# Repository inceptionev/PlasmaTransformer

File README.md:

# Plasma Transformer

## An open-source plasma toroid project by inceptionev (Dr. Bunga)

This project mainly focuses on creating a driver and 3D-printed support structure that allows for safe continuous operation of a plasma toroid.  The objectives are stable operation of a levitating halo of plasma at maximum height above the coil and protection against touching energized components, while providing airflow to keep both the electronics and the globe cool.  The globes are filled with a low-pressure of xenon gas.

### Key Features of this project:
- Plasma Driver PCB with experimentation-friendly features:
  - Wide input power range from 12-60V for easy power control.  Onboard 12V supply for stable fan and gate drive.
  - High-voltage auto-igniter strikes the plasma whenever plasma is not present, but also does not load the driver when plasma is live.  This helps prevent damage from runaway unloaded oscillation.  Designed in collaboration with @ltwin0.
  - Oscillation detector illuminates to show when the driver is in oscillation, whether or not plasma is present.  Based on a design from Sky-guided.
  - Socketed coil and tank capacitor connectors for easy tuning.
  - Dedicated on-board oscilloscope probes on the MOSFET gate and drain nets for Class-E tuning.  Connect an SMA cable directly from the board to a terminator and the oscilloscope.
  - Selectable Gate-Source cap via jumper headers to tune AC gate drive strenth.
  - Separate power switch and DC Gate Bias control.  Turn it off and on without changing the DC gate bias level.
- 3D printed cooling shroud:
  - Provides directed airflow for cooling both the electronics and the globe for continuous use.
  - Supports the fan, board, coil, and globe with ideal spacing for achieving a levitating plasma halo.
  - Provides attachments for rubber bands to hold the globe in place for environments where the device may be in motion, or to attach a shade to make the plasma more visible in outdoor installations.
  - Includes a cover and coil ring that keeps curious fingers away from the hazardous high-voltage parts. (But caution is always advised around high voltage and RF)
- 3D-printed assembly aids:
  - Coil forms for ease of making the plasma coil.

Special thanks to:  
Sky-guided, whose inductive oscillation indicator design is used in this project.  
@ltwin8, whose RF node parasitic auto-igniter design is used in this project and was detailed in https://github.com/inceptionev/PlasmaTransformer/issues/1  

Native design files and manufacturing files in gerber and stl format are provided for the 20cm and 13cm globe sizes.

KiCAD PCB files are found in the /Plasma Transformer PCB folder.  If you want to edit the design, the files are in the folder.  If you just want to make the boards, you need:
- Plasma Transformer PCB/manufacturing/[the zip file with the latest rev]
- Plasma Transformer PCB/bom/[the bom file matching that rev]

Rev 5 PCB specific note:
The holes for the capacitor sockets are too large, so instead of being press-fit, they will need to be soldered in.  I recommend using a piece of paper tape to hold them in place on the top side, then soldering them on the bottom side.  Or you can skip the sockets and solder in the capacitors directly.

3d print design files and a dxf for the heatsink hole pattern are found in the 3D Print and CNC folder.  The heatsink holes are all M3 drill/tap.

If you are doing turnkey PCBA assembly, you probably want to DNP the fan (M1), heatsink (HS1), MOSFET (Q1), and tank capacitors (C1, C16-20) from the BOM in the Turnkey Assembly ZIP package, as you will assemble these later.

If you just want to print the files, look here:
- /3D Print and CNC/20cm Globe STL 3D Print Set
- /3D Print and CNC/13cm Globe STL 3D Print Set

## Additional Materials Needed:
- 12 AWG magnet wire (2mm dia)
- 12mm or 1/2" polyimide (kapton) tape
- 4x M4*30mm self tapping screws
- 4x M4*8mm self tapping screws
- 4x M3 6x6mm Male/Female threaded standoff
- 4x M3 6mm screws to mount PCB to heatsink
- M3 washers and lockwashers
- JST XHP-2 connector and contacts for fan
- The appropriate capacitor values from the list below
- Thermal pad for TO-247 MOSFET (example: SPK4-0.006-00-104)
- M3*20mm screw, washer, and lockwasher for mounting MOSFET
- 4mm OD x 2.5mm ID PTFE tube (commonly sold as Bowden tube for 1.75mm filament 3D printers)

## Assembly instructions:
- I recommend 3D-printing the coil forms and the spacer ring first, then the cooling shroud, cover, and foot.  You may also want to print a smaller coil form for pre-winding in the first batch, see coil instructions below.
- The main cooling shroud may take 20+ hrs to print, so you can build the heatsink, coil and PCB while it is printing.
- Prepare the heatsink
  - Drill and tap the holes in the heatsink.  They are all M3.  A DXF is provided if you wnat to use a CNC.
  - Mount the MOSFET into the heatsink with thermal pad LOOSELY (do not tighten yet)
  - Bend the MOSFET pins up 90 degrees
  - Install the standoffs into the heatsink
- Assemble the PCB per the BOM EXCEPT for the MOSFET.  That component will be soldered last.
- Mount the PCB to the heatsink with 4x M3x6mm screws, washers, and lockwashers, threading the MOSFET pins through the holes in the board.  Make sure the MOSFET is loose so it can move into alighment with the board.
- Tighten the screws mounting the PCB to the heatsink first.
- Then tighten the mounting screw of the MOSFET to the heatsink.
- Solder the MOSFET in.
- Add connector to the fan.  Pin 1 is positive.
- Make the coil
  - Print out the coil form in the folder for the globe size you are using.
  - Push a length of 12AWG magnet wire in a length of insulating PTFE tube.  It helps if the tube and the wire are both straight.  Taping them to the edge of a table will accomplish this.
    - For the 13cm globe, push 171.6cm of wire into 151.6cm of PTFE tube.  Leave 10cm of wire sticking out at both ends.
	- For the 20cm globe, push 203cm of wire into 175cm of of PTFE tube.  Leave 14cm of wire sticking out at both ends.
  - First wrap the wire and insulator around an object slightly smaller than the coil form.  This will make wrapping on the coil form easier.  You can use the 13cm coil form as the pre-wind form for the 20cm coil. An stl file for an 80mm coil form is also provided to act as the pre-wind for the 13cm coil.
  - Wrap the slightly-smaller coil of wire and insulator onto the coil form.  Start at the lip, and work up from there in a clockwise direction with the lip facing away from you.  This ensures that the bottom coil connects to the RF Node (the right block on the PCB).  This is the higher voltage terminal, and having it on the bottom coil helps with levitation of the plasma.
    - 13cm Globe: you should get 4 coils, minus the 9mm gap where the ends meet.
	- 20cm Globe: you should get 3 coils, minus the 9mm gap where the ends meet.
  - Use the slots in the coil form to tape up the coil so it holds its shape.  Polyimide (Kapton) tape is recommended.
  - Remove the coil from the form and wrap the coil again where the tail meets the coil
  - Open the coil terminal latches on the PCB and fit the coil into the assembly with the PCB, making bends to allow for the envelope of the globe.  Make an 'S' curve at the bottom of the coil wires where they exit the PCB blocks, to allow for adjusting the height.
  - Trim the coil tails if necessary.
  - Burn about 12mm of insulation off the end of the coil tails and clean it up with sandpaper until you can see the shiny copper underneath.  A lighter works well for this.
  - Install the coil spacer ring into the top of the coil, opposite of the direction where the wire tails go.
- Mount the foot and the fan to the bottom with the M4*30mm screws, threading the fan wires through the notch in the bottom.  
- Connect the fan to the PCB.  On the 20mm cooling shroud, a slot is provided in the wall next to the PCB to hold the fan connector temporarily for easy connecting and disconnecting.
- Mount the PCB to the cooling shroud with the M4*8mm screws
- Latch the coil into the PCB.
- Screw in 5x M4x8mm screws into the bosses around the circumference of the cooling shroud. This can be used for shrouds or rubber bands to secure the globe.
- Optionally install the cover into the cooling shroud.

## Known successful values from experimentation:

Supply Voltage:
- 20cm Globe: 24V
- 13cm Globe: 19V

Gate-Drain Cap:
- 20cm Globe: none
- 13cm Globe: none

Resonant Cap:
- 20cm Globe: 3x 24pF 564RC0GAJ602EJ240J
- 13cm Globe: 3x 24pF 564RC0GAJ602EJ240J

Gate-Source Cap:
- 20cm Globe: 2.7nF + 3.6nF + 1.8nF + 1.8nF
- 13cm Globe: 2.7nF

Measured Air Core Inductance of Globe Coils (no globe or plasma present):
- 13cm Globe, 4 turns 122mm x 16mm long: 3.3uH
- 20cm Globe, 3 turns 187mm dia x 12mm long: 3.6uH

## Tips and Tricks for Experimenting with Plasma Toroids:
- The goal of feedback tuning is to minimize the source-drain voltage across the MOSFET during the points of switching, otherwise it will get hot quickly.
- Also be mindful of the voltage rating on the cap between the plasma globe coil and the gate.  This cap will see 1000V+ when the coil is unloaded (when there is no plasma).
- Also be careful of anything in that node.  That means anything between the gate-coil capacitor and the coil, including the bottom turns of the coil.  This is the HF node, aka RF node, where the highest amplitude of voltage oscillation is seen.  It will burn you if you touch it, sometimes even touching insulated portions.  The burn is nearly painless at first, and then painful later.
- The MOSFET and the coil-gate cap are the two most common components to break in this circuit.
- Haloplasma is a good source for the xenon-filled plasma globes.

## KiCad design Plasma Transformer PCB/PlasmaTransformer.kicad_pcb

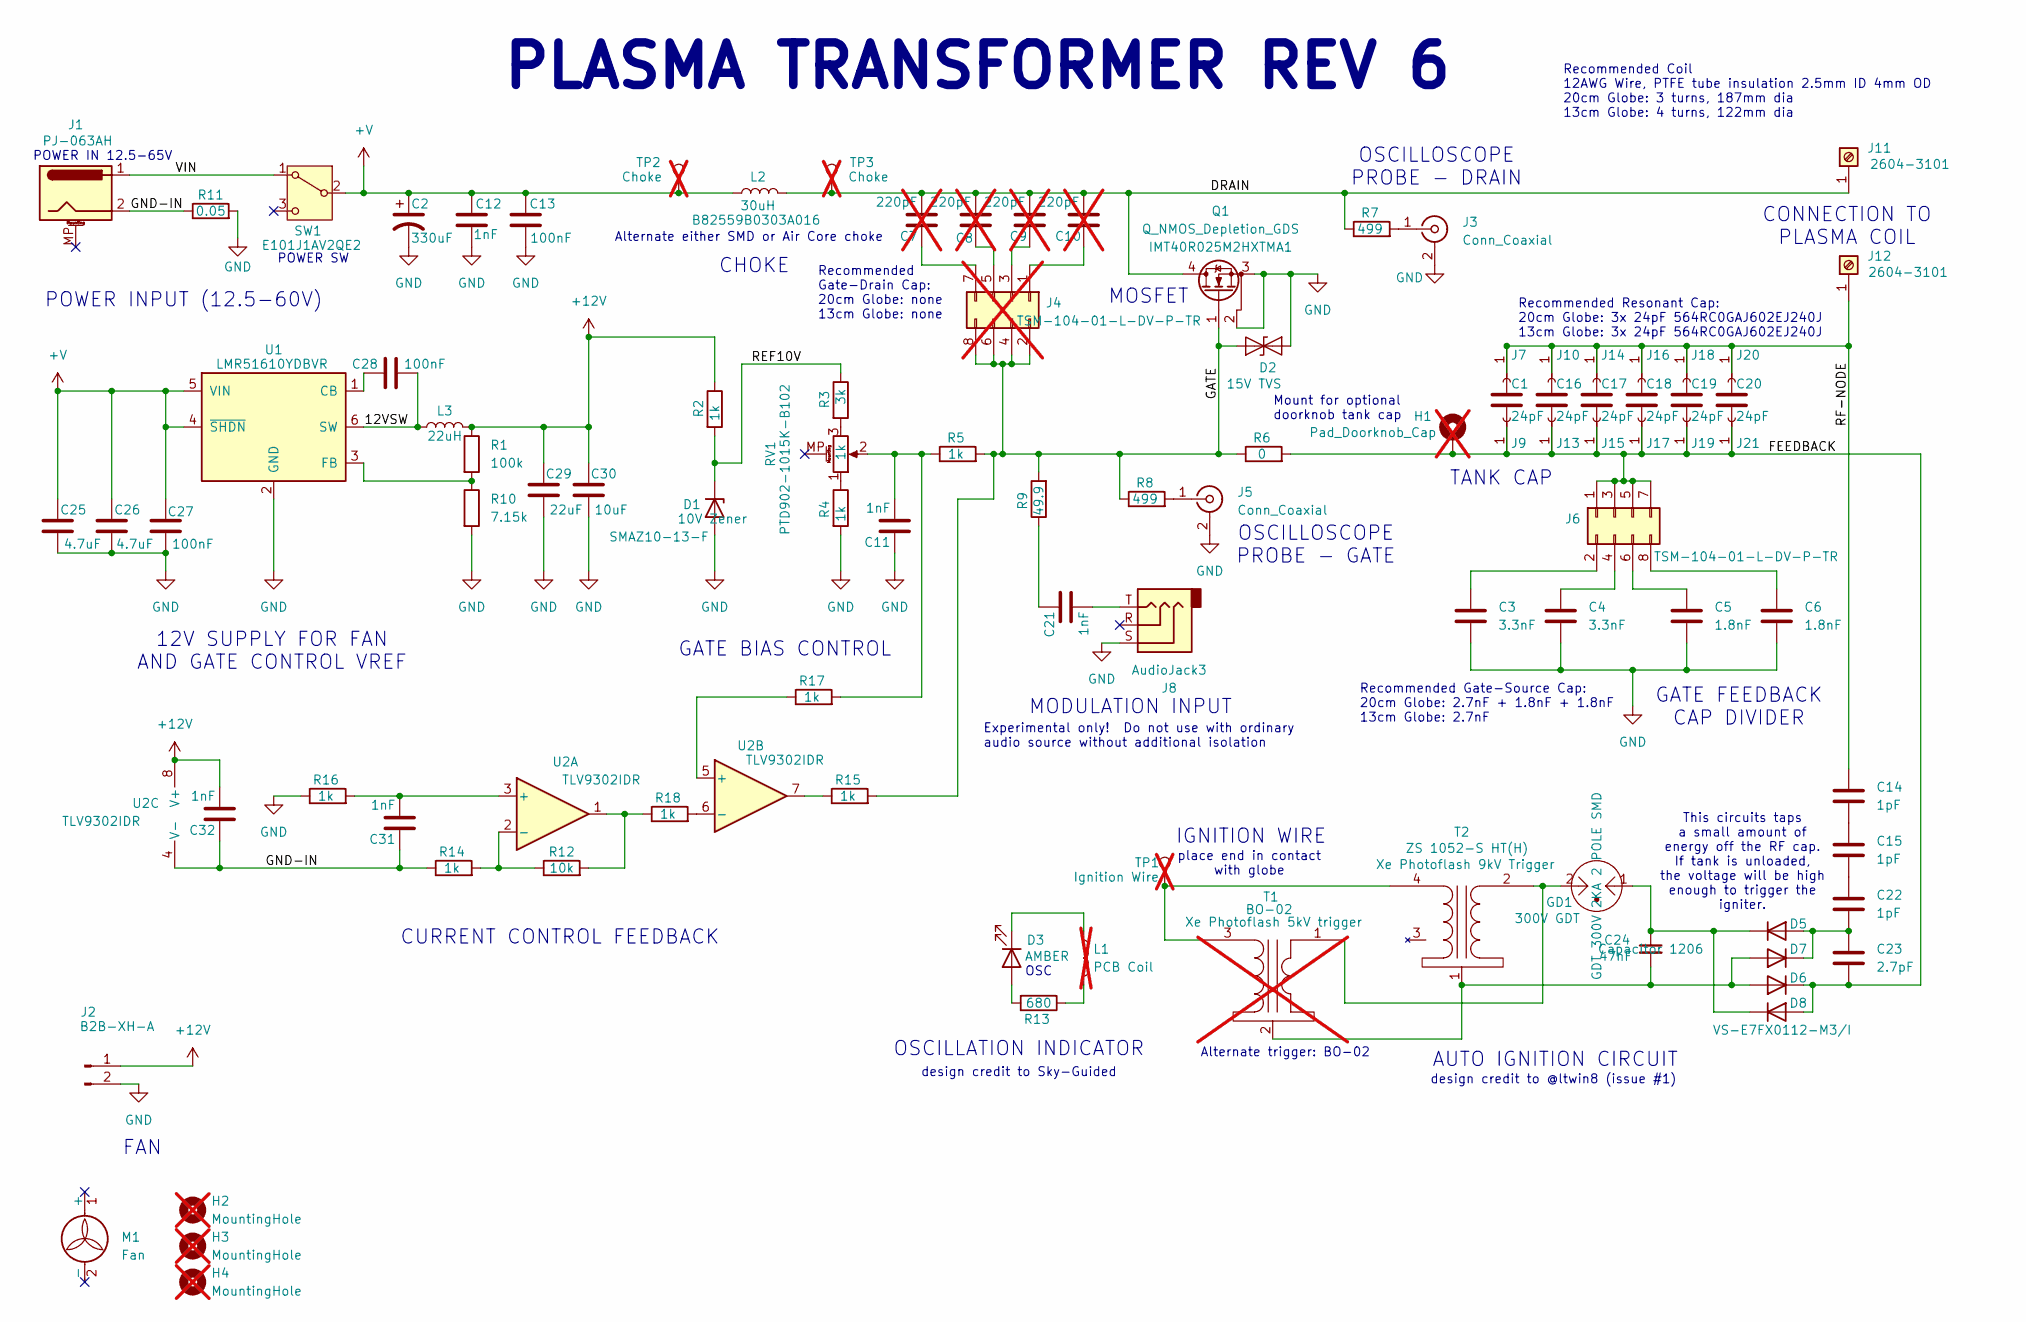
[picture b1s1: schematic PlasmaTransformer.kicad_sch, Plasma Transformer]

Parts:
C1, C16, C17, C18, C19, C20: 24pF; C_Disc_D11.0mm_W5.0mm_P10.00mm; Voltage 6000V; MPN 564RC0GAJ602EJ240J
C2: 330uF; CP_Elec_16x17.5_FK_Series; Voltage 80V; MPN EEV-FK1K331M
C3, C4: 3.3nF; C_1206_3216Metric; Voltage 250V; MPN C3216C0G2E332K085AA
C5, C6: 1.8nF; C_1206_3216Metric; Voltage 630V; MPN CC1206JKNPOZBN182
C7, C8, C9, C10: 220pF; C_1206_3216Metric; Voltage 1000V; MPN VJ1206A221JBGTW1HV; not fitted
C11, C12, C21, C31, C32: 1nF; C_0805_2012Metric; Voltage 100V; MPN CL21C102JCFNNNE
C13: 100nF; C_1812_4532Metric; Voltage 1000V; MPN GRM43DR7LW104KW01K
C14, C15, C22: 1pF; C_1210_3225Metric; Voltage 2000V; MPN 111122K01P00BQTAF9LM
C23: 2.7pF; C_1210_3225Metric; Voltage 2000V; MPN 111122K02P70HQTAF9LM
C24: 47nF; C_1206_3216Metric; Voltage 500V; MPN C1206C473KCRACTU
C25, C26: 4.7uF; C_1210_3225Metric; Voltage 100V; MPN CL32B475KCVZW6E
C27, C28: 100nF; C_0805_2012Metric; Voltage 100V; MPN C2012X7R2A104K125AA
C29: 22uF; C_0805_2012Metric; Voltage 25V; MPN CL21A226MAYNNNE
C30: 10uF; C_0805_2012Metric; Voltage 25V; MPN CL21A106KAYNNNE
D1: 10V Zener; D_SMA; MPN SMAZ10-13-F
D2: 15V TVS; D_SMC; MPN 5.0SMDJ15CA
D3: AMBER; LED_1206_3216Metric; MPN 150120AS75000
D5, D6, D7, D8: D; D_SMF; Voltage 1200V; MPN VS-E7FX0112-M3/I
GD1: 300V GDT; L_1812_4532Metric; MPN 2051-30-SM-RPLF
H1: Pad_Doorknob_Cap; MountingHole_5.3mm_M5_Pad; not fitted
H2, H3, H4: MountingHole; MountingHole_3.2mm_M3; not fitted
J1: Barrel_Jack_MountingPin; BarrelJack_CUI_PJ-063AH_Horizontal; MPN PJ-063AH
J2: Conn_01x02_Pin; JST_XH_B2B-XH-A_1x02_P2.50mm_Vertical; MPN B2B-XH-A
J3, J5: Conn_Coaxial; SMA_Amphenol_901-144_Vertical; MPN RFPC-SMA28-F
J4: Conn_02x04_Odd_Even; PinHeader_2x04_P2.54mm_Vertical_SMD; MPN TSM-104-01-L-DV-P-TR; not fitted
J6: Conn_02x04_Odd_Even; PinHeader_2x04_P2.54mm_Vertical_SMD; MPN TSM-104-01-L-DV-P-TR
J7, J9, J10, J13, J14, J15, J16, J17, J18, J19, J20, J21: Conn_01x01_Socket; H8501-05; MPN H8501-05
J8: AudioJack3; Jack_3.5mm_CUI_SJ-3523-SMT_Horizontal; MPN SJ-3523-SMT-TR
J11, J12: Screw_Terminal_01x01; CONN_2604-3101_WAG; MPN 2604-3101
L1: PCB Coil; FEEDBACK_COIL_B; not fitted
L2: 30uH; B82559B_TDK; MPN B82559B0303A016
L3: 22uH; L_Pana_PCC-KVP_5.5x5mm; MPN ETQ-P3M220KVP
M1: Fan; FAN AXIAL 92X25.4MM; MPN AFB0912VHD-F00
Q1: Q_NMOS_Depletion_GDS; IMT40R025M2HXTMA1; MPN IMT40R025M2HXTMA1
R1: 100k; R_0805_2012Metric; Tolerance 1%; MPN RC0805FR-07100KL
R2, R4, R5, R14, R15, R16, R17, R18: 1k; R_0805_2012Metric; Tolerance 1%; MPN RC0805FR-071KL
R3: 3k; R_0805_2012Metric; Tolerance 1%; MPN RC0805FR-073KL
R6: 0; R_1812_4532Metric; Tolerance 1%; MPN ERJ-12Y0R00U
R7, R8: 499; R_2010_5025Metric; Tolerance 1%; MPN RC2010FK-07499RL
R9: 49.9; R_2010_5025Metric; Tolerance 1%; MPN RC2010FK-0749R9L
R10: 7.15k; R_0805_2012Metric; Tolerance 1%; MPN RC0805FR-077K15L
R11: 0.05; R_2512_6332Metric; MPN CRA2512-FZ-R050ELF
R12: 10k; R_0805_2012Metric; Tolerance 1%; MPN RC0805FR-0710KL
R13: 680; R_0805_2012Metric; Tolerance 1%; MPN RC0805FR-07680RL
RV1: 1k; Bourns-Potentiometer-PTD902-2; MPN PTD902-1015K-B102
SW1: SW_SPDT; CKSW-E101J1AV2QE2; MPN E101J1AV2QE2
T1: BO-02; MPN BO-02; not fitted
T2: ZS 1052-S HT(H); MPN ZS 1052-S HT(H)
TP1: Ignition Wire; SolderWire-0.75sqmm_1x01_D1.25mm_OD2.3mm; not fitted
TP2, TP3: Choke; SolderWire-1sqmm_1x01_D1.4mm_OD2.7mm; not fitted
U1: LMR51610YDBVR; SOT-23-6; MPN LMR51610YDBVR
U2: TLV9302IDR; SOIC-8_3.9x4.9mm_P1.27mm; MPN TLV9302IDR

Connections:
+12V: C29.2, C30.2, C32.2, J2.1, L3.2, R1.1, R2.1, U2.8 (V+)
+V: C2.1, C12.2, C13.2, C25.1, C26.1, C27.2, L2.1, SW1.2 (B), TP2.1, U1.4 (~SHDN), U1.5 (VIN)
/12VSW: C28.1, L3.1, U1.6 (SW)
/FEEDBACK: C1.2, C16.2, C17.2, C18.2, C19.2, C20.2, C23.2, D6.1 (K), D8.2 (A), H1.1, J6.1, J6.3, J6.5, J6.7, J9.1, J13.1, J15.1, J17.1, J19.1, J21.1, R6.2
/GATE: D2.1 (A1), J4.2, J4.4, J4.6, J4.8, Q1.1 (G), R5.2, R6.1, R8.1, R9.2, R15.2
/GND-IN: C31.1, C32.1, J1.2, R11.1, R14.1, U2.4 (V-)
/REF10V: D1.1 (K), R2.2, R3.1
/RF-NODE: C1.1, C14.1, C16.1, C17.1, C18.1, C19.1, C20.1, J7.1, J10.1, J12.1, J14.1, J16.1, J18.1, J20.1
/VIN: J1.1, SW1.1 (A)
unnamed: C11.2, R5.1, R17.2, RV1.2
unnamed: C14.2, C15.1
unnamed: C15.2, C22.1
unnamed: C21.1, R9.1
unnamed: C21.2, J8.T
unnamed: D3.2 (A), R13.2
unnamed: D3.1 (K), L1.1
unnamed: C22.2, C23.1, D5.2 (A), D7.1 (K)
unnamed: C24.1, D5.1 (K), D8.1 (K), GD1.1
unnamed: C24.2, D6.2 (A), D7.2 (A), T1.2 (AB), T2.1 (AB)
unnamed: J3.1 (In), R7.2
unnamed: C10.1, J4.1
unnamed: C9.1, J4.3
unnamed: C8.1, J4.5
unnamed: C7.1, J4.7
unnamed: J5.1 (In), R8.2
unnamed: C3.1, J6.2
unnamed: C4.1, J6.4
unnamed: C5.1, J6.6
unnamed: C6.1, J6.8
unnamed: L1.2, R13.1
unnamed: R3.2, RV1.3
unnamed: R4.1, RV1.1
unnamed: R12.2, R18.1, U2.1
unnamed: R15.1, U2.7
unnamed: GD1.2, T1.1 (Primary), T2.2 (AA)
unnamed: T1.3 (Secondary), T2.4 (SB), TP1.1
unnamed: C28.2, U1.1 (CB)
unnamed: R1.2, R10.1, U1.3 (FB)
unnamed: C31.2, R16.2, U2.3 (+)
unnamed: R12.1, R14.2, U2.2 (-)
unnamed: R17.1, U2.5 (+)
unnamed: R18.2, U2.6 (-)

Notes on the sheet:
GATE BIAS CONTROL
12V SUPPLY FOR FAN AND GATE CONTROL VREF
IGNITION WIRE
AUTO IGNITION CIRCUIT
design credit to @ltwin8 (issue #1)
This circuits taps a small amount of energy off the RF cap. If tank is unloaded, the voltage will be high enough to trigger the igniter.
POWER INPUT (12.5-60V)
OSCILLOSCOPE PROBE - GATE
OSCILLATION INDICATOR
CHOKE
Recommended Resonant Cap: 20cm Globe: 3x 24pF 564RC0GAJ602EJ240J 13cm Globe: 3x 24pF 564RC0GAJ602EJ240J
Alternate trigger: BO-02
CONNECTION TO PLASMA COIL
Recommended Coil 12AWG Wire, PTFE tube insulation 2.5mm ID 4mm OD 20cm Globe: 3 turns, 187mm dia 13cm Globe: 4 turns, 122mm dia
MODULATION INPUT
POWER IN 12.5-65V
Experimental only! Do not use with ordinary audio source without additional isolation
MOSFET
PLASMA TRANSFORMER REV 6
design credit to Sky-Guided
CURRENT CONTROL FEEDBACK
Recommended Gate-Drain Cap: 20cm Globe: none 13cm Globe: none
GATE FEEDBACK CAP DIVIDER
POWER SW
place end in contact with globe
OSC
Recommended Gate-Source Cap: 20cm Globe: 2.7nF + 1.8nF + 1.8nF 13cm Globe: 2.7nF
Mount for optional doorknob tank cap
Alternate either SMD or Air Core choke
OSCILLOSCOPE PROBE - DRAIN
TANK CAP
FAN

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
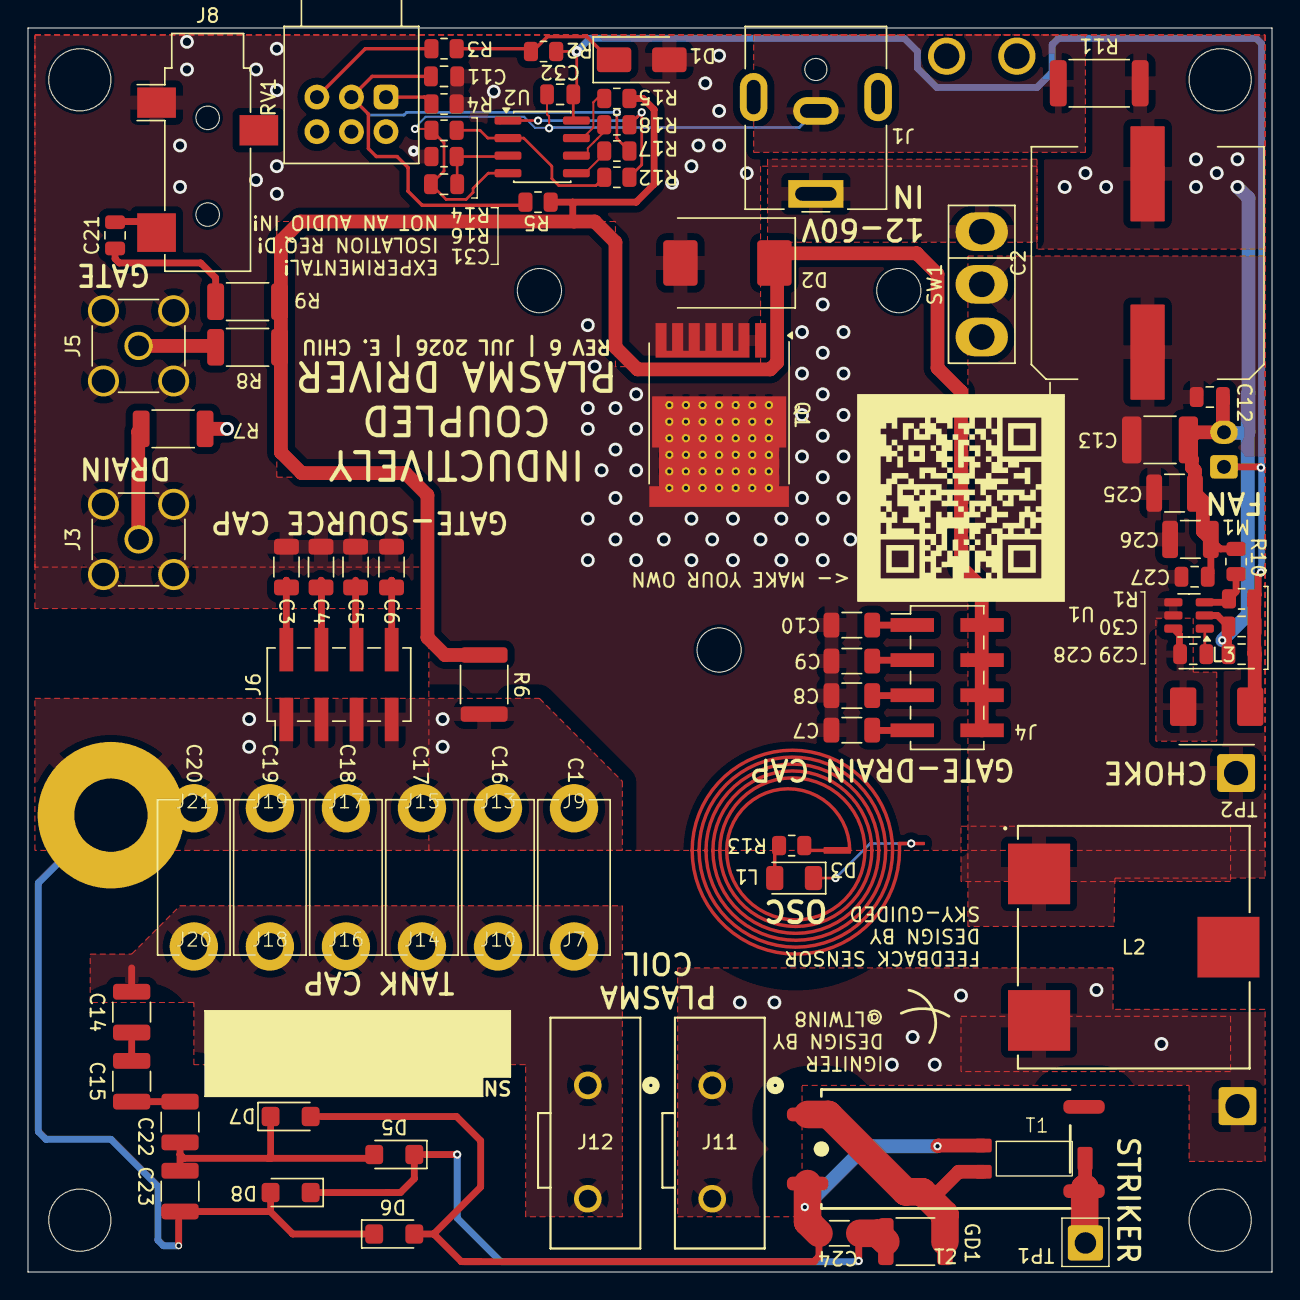
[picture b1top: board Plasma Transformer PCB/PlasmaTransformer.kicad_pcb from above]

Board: 2 copper layers, 90.0 x 90.0 mm, 97 parts (1 on the bottom side), 44 nets.

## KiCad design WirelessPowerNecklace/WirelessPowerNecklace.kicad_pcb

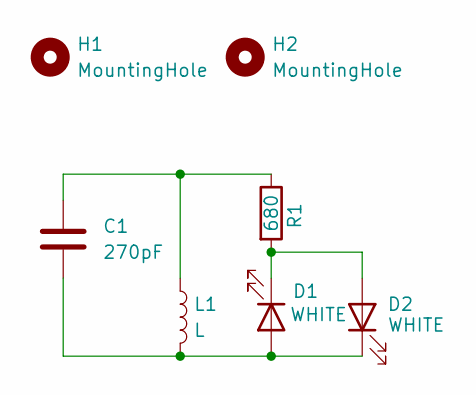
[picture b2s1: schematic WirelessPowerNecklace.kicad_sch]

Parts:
C1: 270pF; C_1206_3216Metric; MPN CL31C271JIHNNNE
D1, D2: WHITE; LED_1206_3216Metric; MPN LTW-150TK
H1, H2: MountingHole; MountingHole_2.1mm
L1: L; PCB-Coil-ID15mm-6T
R1: 680; R_1206_3216Metric; MPN RC0805FR-07680RL

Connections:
unnamed: C1.1, L1.1, R1.1
unnamed: C1.2, D1.2 (A), D2.1 (K), L1.2
unnamed: D1.1 (K), D2.2 (A), R1.2

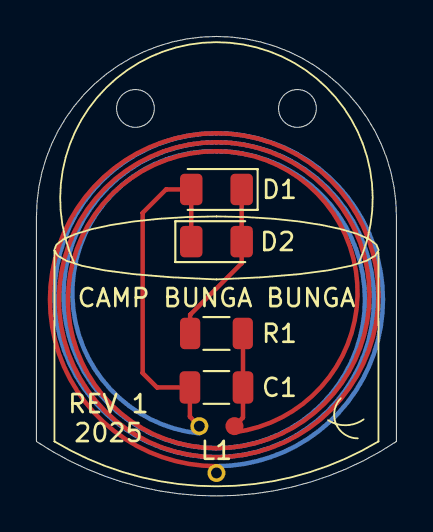
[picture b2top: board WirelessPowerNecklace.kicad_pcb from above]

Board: 2 copper layers, 20.0 x 25.5 mm, 7 parts (0 on the bottom side), 3 nets.

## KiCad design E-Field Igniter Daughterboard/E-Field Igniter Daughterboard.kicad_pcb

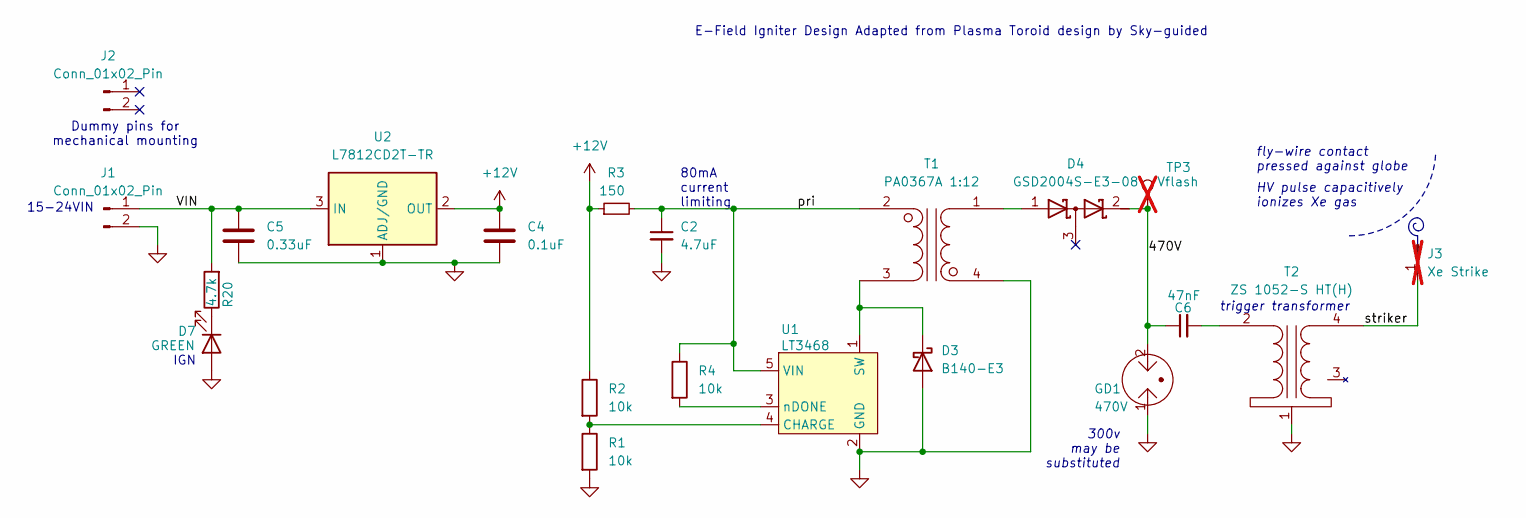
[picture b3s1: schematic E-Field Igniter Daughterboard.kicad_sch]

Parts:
C2: 4.7uF; C_1206_3216Metric; MPN C3216X7R1E475K160AC
C4: 0.1uF; C_0805_2012Metric; MPN KGM21NR71H104KT
C5: 0.33uF; C_0805_2012Metric; MPN CL21B334KBFNNNE
C6: 47nF; C_1206_3216Metric; MPN C1206C473KCRACTU
D3: B140-E3; D_SMA; MPN B140-E3/61T
D4: GSD2004S-E3-08; SOT-23; MPN GSD2004S-E3-08
D7: GREEN; LED_1206_3216Metric; MPN 150120VS75000
GD1: 470V; L_1812_4532Metric; MPN 2051-30-SM-RPLF
J1, J2: Conn_01x02_Pin; PinHeader_1x02_P1.00mm_Vertical; MPN M20-9990245
J3: Xe Strike; SolderWire-1sqmm_1x01_D1.4mm_OD2.7mm; not fitted
R1, R2, R4: 10k; R_0805_2012Metric; MPN RC0805FR-1310KP
R3: 150; R_0805_2012Metric; MPN RC0805FR-07150RL
R20: 4.7k; R_0805_2012Metric; MPN RC0805FR-134K7L
T1: PA0367A 1:12; PA0367A; MPN PA0367ANLT
T2: ZS 1052-S HT(H); MPN ZS 1052-S HT(H)
TP3: Vflash; TestPoint_THTPad_D2.0mm_Drill1.0mm; not fitted
U1: LT3468; SOT-23-5; MPN LT3468ES5-1#TRMPBF
U2: L7812CD2T-TR; TO-263-2; MPN L7812CD2T-TR

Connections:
+12V: C4.1, R2.1, R3.1, U2.2 (OUT)
/470V: C6.1, D4.2 (K), GD1.2, TP3.1
/VIN: C5.1, J1.1, R20.2, U2.3 (IN)
/pri: C2.1, R3.2, R4.1, T1.2 (AA), U1.5 (VIN)
/striker: J3.1, T2.4 (SB)
GND: C2.2, C4.2, C5.2, D3.2 (A), D7.2 (A), GD1.1, J1.2, R1.2, T1.4 (SA), T2.1 (AB), U1.2 (GND), U2.1 (ADJ/GND)
unnamed: D3.1 (K), T1.3 (AB), U1.1 (SW)
unnamed: D4.1 (A), T1.1 (SB)
unnamed: D7.1 (K), R20.1
unnamed: C6.2, T2.2 (AA)
unnamed: R1.1, R2.2, U1.4 (CHARGE)
unnamed: R4.2, U1.3 (nDONE)

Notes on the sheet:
IGN
80mA current limiting
300v may be substituted
trigger transformer
15-24VIN
Dummy pins for mechanical mounting
E-Field Igniter Design Adapted from Plasma Toroid design by Sky-guided
HV pulse capacitively ionizes Xe gas
fly-wire contact pressed against globe

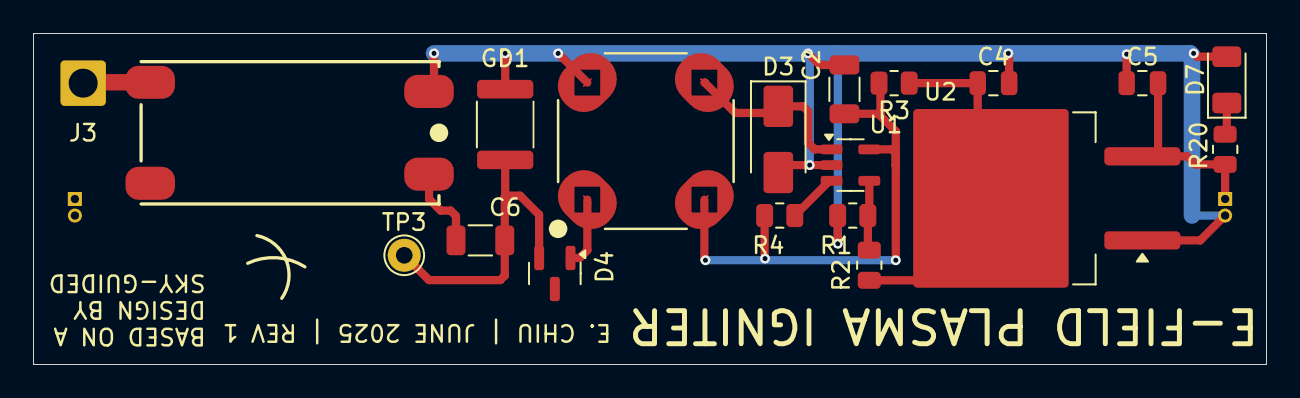
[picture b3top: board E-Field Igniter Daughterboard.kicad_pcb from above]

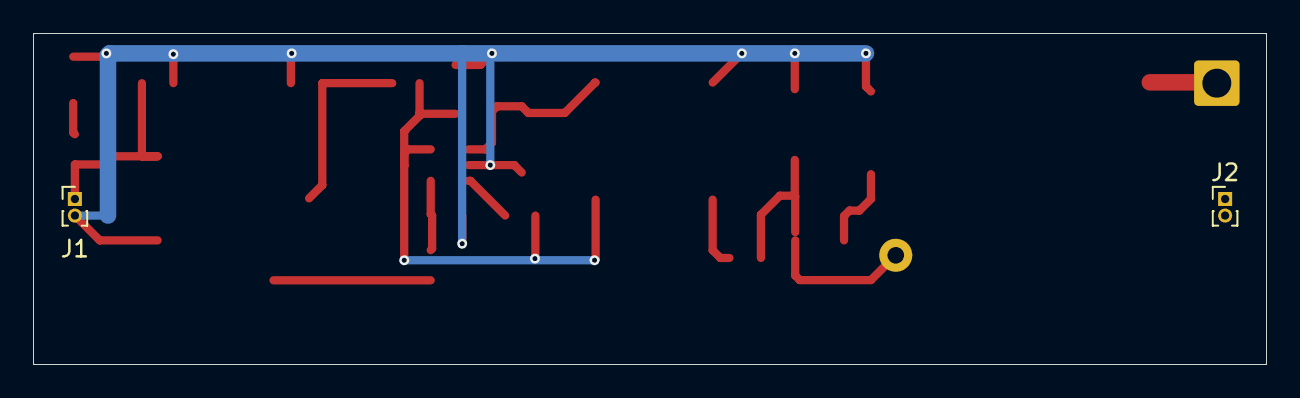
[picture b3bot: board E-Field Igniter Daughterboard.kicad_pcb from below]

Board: 2 copper layers, 74.5 x 20.0 mm, 21 parts (2 on the bottom side), 12 nets.

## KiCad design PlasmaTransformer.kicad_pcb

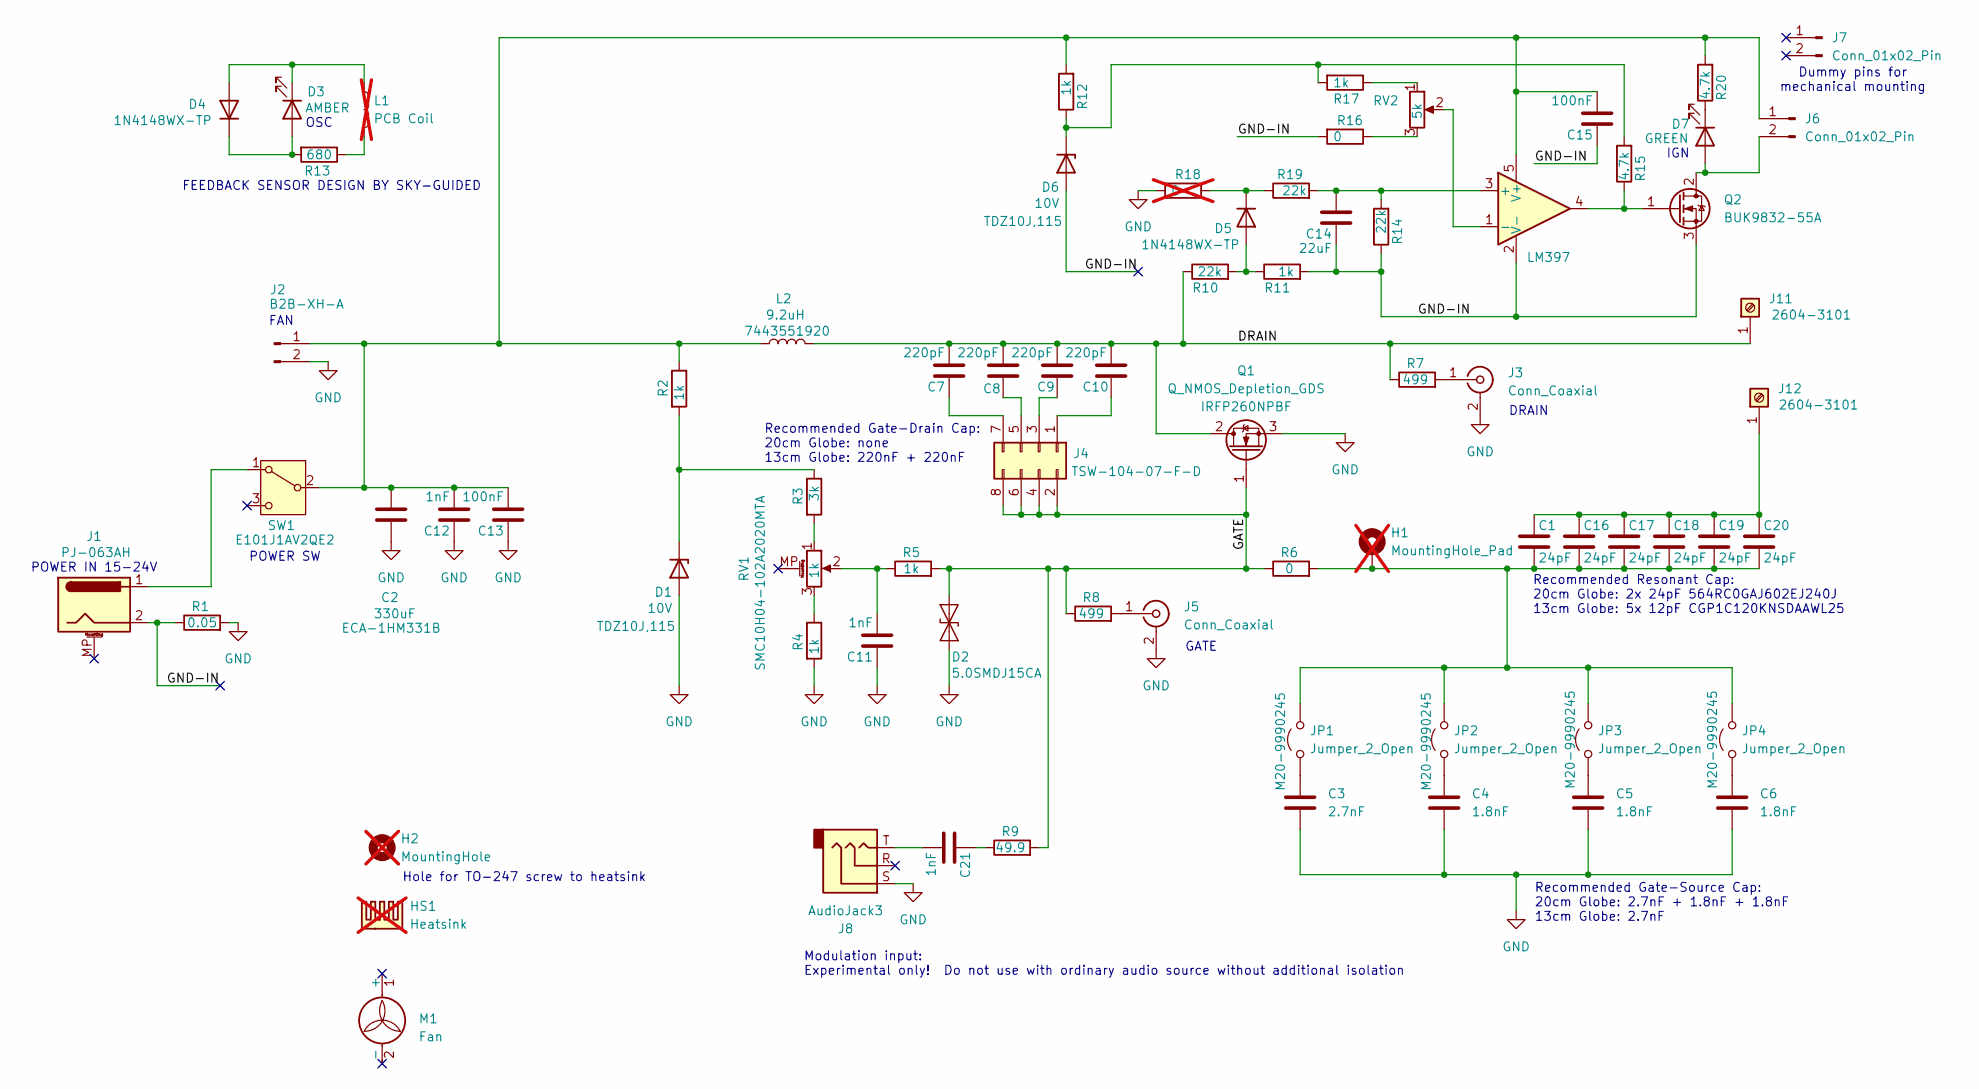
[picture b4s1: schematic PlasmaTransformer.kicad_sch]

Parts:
C1, C16, C17, C18, C19, C20: 24pF; C_Disc_D11.0mm_W5.0mm_P10.00mm; MPN 564RC0GAJ602EJ240J
C2: 330uF; CP_Radial_D10.0mm_P5.00mm; MPN ECA-1HM331B
C3: 2.7nF; C_1812_4532Metric; MPN 1812GC272KAT1A
C4, C5, C6: 1.8nF; C_1812_4532Metric; MPN C1812C182JCGACTU
C7, C8, C9, C10: 220pF; C_1812_4532Metric; MPN CC1812JKNPOCBN221
C11, C12, C21: 1nF; C_1812_4532Metric; MPN VJ1812A102JXFTW1HV
C13: 100nF; C_1812_4532Metric; MPN GRM43DR7LW104KW01K
C14: 22uF; C_0805_2012Metric; MPN GRM21BR61E226ME44L
C15: 100nF; C_0805_2012Metric; MPN CL21B104KCFNNNE
D1, D6: 10V; D_SOD-323_HandSoldering; MPN TDZ10J,115
D2: 5.0SMDJ15CA; D_SMC; MPN 5.0SMDJ15CA
D3: AMBER; LED_1206_3216Metric; MPN 150120AS75000
D4, D5: D; D_SOD-323; MPN 1N4148WX-TP
D7: GREEN; LED_1206_3216Metric; MPN 150120VS75000
H1: MountingHole_Pad; MountingHole_5.3mm_M5_Pad; not fitted
H2: MountingHole; MountingHole_8.4mm_M8; not fitted
HS1: Heatsink; Heatsink_75x37.5mm_Fischer_SK-594-37.5-AL; not fitted
J1: Barrel_Jack_MountingPin; BarrelJack_CUI_PJ-063AH_Horizontal; MPN PJ-063AH
J2: Conn_01x02_Pin; JST_XH_B2B-XH-AM_1x02_P2.50mm_Vertical; MPN B2B-XH-A
J3, J5: Conn_Coaxial; SMA_Amphenol_901-143_Horizontal; MPN RFPC-SMA27-F
J4: Conn_02x04_Odd_Even; PinHeader_2x04_P2.54mm_Vertical; MPN TSW-104-07-F-D
J6, J7: Conn_01x02_Pin; PinHeader_1x02_P2.54mm_Vertical; MPN ESQ-102-33-G-S
J8: AudioJack3; Jack_3.5mm_CUI_SJ-3523-SMT_Horizontal; MPN SJ-3523-SMT-TR
J11, J12: Screw_Terminal_01x01; CONN_2604-3101_WAG; MPN 2604-3101
JP1, JP2, JP3, JP4: Jumper_2_Open; PinHeader_1x02_P2.54mm_Vertical; MPN M20-9990245
L1: PCB Coil; FEEDBACK_COIL_B; not fitted
L2: 9.2uH; L_APV_APH1770; MPN 7443551920
M1: Fan; FAN AXIAL 92X25.4MM; MPN AFB0924VH-R00
Q1: Q_NMOS_Depletion_GDS; TO-247-3_Horizontal_TabDown; MPN IRFP260NPBF
Q2: BUK9832-55A; SOT-223-3_TabPin2; MPN BUK9832-55A/CUX
R1: 0.05; R_2512_6332Metric; MPN CRA2512-FZ-R050ELF
R2, R4, R5, R11, R12, R17: 1k; R_0805_2012Metric; MPN RC0805FR-071KL
R3: 3k; R_0805_2012Metric; MPN RC0805FR-073KL
R6: 0; R_1812_4532Metric; MPN ERJ-12Y0R00U
R7, R8: 499; R_2010_5025Metric; MPN RC2010FK-07499RL
R9: 49.9; R_2010_5025Metric; MPN RC2010FK-0749R9L
R10, R14, R19: 22k; R_0805_2012Metric; MPN RC0805FR-1322KL
R13: 680; R_0805_2012Metric; MPN RC0805FR-07680RL
R15, R20: 4.7k; R_0805_2012Metric; MPN RC0805FR-134K7L
R16: 0; R_0805_2012Metric; MPN RC0805JR-070RL
R18: 0; R_0805_2012Metric; MPN RC0805JR-070RL; not fitted
RV1: 1k; SMC10H04-102A2020MTA; MPN SMC10H04-102A2020MTA
RV2: 5k; Potentiometer_Vishay_TS53YL_Vertical; MPN TS53YL502MR10
SW1: SW_SPDT; CKSW-E101J1AV2QE2; MPN E101J1AV2QE2
U1: LM397; SOT-23-5; MPN LM397MF/NOPB

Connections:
/DRAIN: C7.2, C8.2, C9.2, C10.2, J11.1, L2.2, Q1.2 (D), R7.1, R10.1
/GATE: D2.1 (A1), J4.2, J4.4, J4.6, J4.8, Q1.1 (G), R5.2, R6.1, R8.1, R9.2
/GND-IN: C14.1, C15.1, D6.2 (A), J1.2, Q2.3 (S), R1.1, R11.2, R14.1, R16.2, U1.2 (V-)
GND: C2.2, C3.2, C4.2, C5.2, C6.2, C11.1, C12.1, C13.1, D1.2 (A), D2.2 (A2), J2.2, J3.2 (Ext), J5.2 (Ext), J8.S, Q1.3 (S), R1.2, R4.2, R18.2
unnamed: C11.2, R5.1, RV1.2
unnamed: C21.1, R9.1
unnamed: C21.2, J8.T
unnamed: D1.1 (K), R2.2, R3.1
unnamed: D3.2 (A), D4.1 (K), R13.2
unnamed: D3.1 (K), D4.2 (A), L1.1
unnamed: D5.2 (A), R10.2, R11.1
unnamed: D5.1 (K), R18.1, R19.1
unnamed: D6.1 (K), R12.1, R15.2, R17.2
unnamed: D7.2 (A), J6.2, Q2.2 (D)
unnamed: D7.1 (K), R20.1
unnamed: C2.1, C12.2, C13.2, C15.2, J2.1, J6.1, L2.1, R2.1, R12.2, R20.2, SW1.2 (B), U1.5 (V+)
unnamed: J3.1 (In), R7.2
unnamed: C10.1, J4.1
unnamed: C9.1, J4.3
unnamed: C8.1, J4.5
unnamed: C7.1, J4.7
unnamed: J5.1 (In), R8.2
unnamed: C1.1, C16.1, C17.1, C18.1, C19.1, C20.1, J12.1
unnamed: C3.1, JP1.1 (A)
unnamed: C1.2, C16.2, C17.2, C18.2, C19.2, C20.2, H1.1, JP1.2 (B), JP2.2 (B), JP3.2 (B), JP4.2 (B), R6.2
unnamed: C4.1, JP2.1 (A)
unnamed: C5.1, JP3.1 (A)
unnamed: C6.1, JP4.1 (A)
unnamed: L1.2, R13.1
unnamed: Q2.1 (G), R15.1, U1.4
unnamed: R3.2, RV1.1
unnamed: R4.1, RV1.3
unnamed: R16.1, RV2.3
unnamed: R17.1, RV2.1
unnamed: J1.1, SW1.1 (A)
unnamed: C14.2, R14.2, R19.2, U1.3 (+)
unnamed: RV2.2, U1.1 (-)

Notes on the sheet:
Hole for TO-247 screw to heatsink
FEEDBACK SENSOR DESIGN BY SKY-GUIDED
Recommended Resonant Cap: 20cm Globe: 2x 24pF 564RC0GAJ602EJ240J 13cm Globe: 5x 12pF CGP1C120KNSDAAWL25
POWER IN 15-24V
Modulation input: Experimental only! Do not use with ordinary audio source without additional isolation
Dummy pins for mechanical mounting
GATE
Recommended Gate-Drain Cap: 20cm Globe: none 13cm Globe: 220nF + 220nF
DRAIN
POWER SW
IGN
OSC
Recommended Gate-Source Cap: 20cm Globe: 2.7nF + 1.8nF + 1.8nF 13cm Globe: 2.7nF
FAN

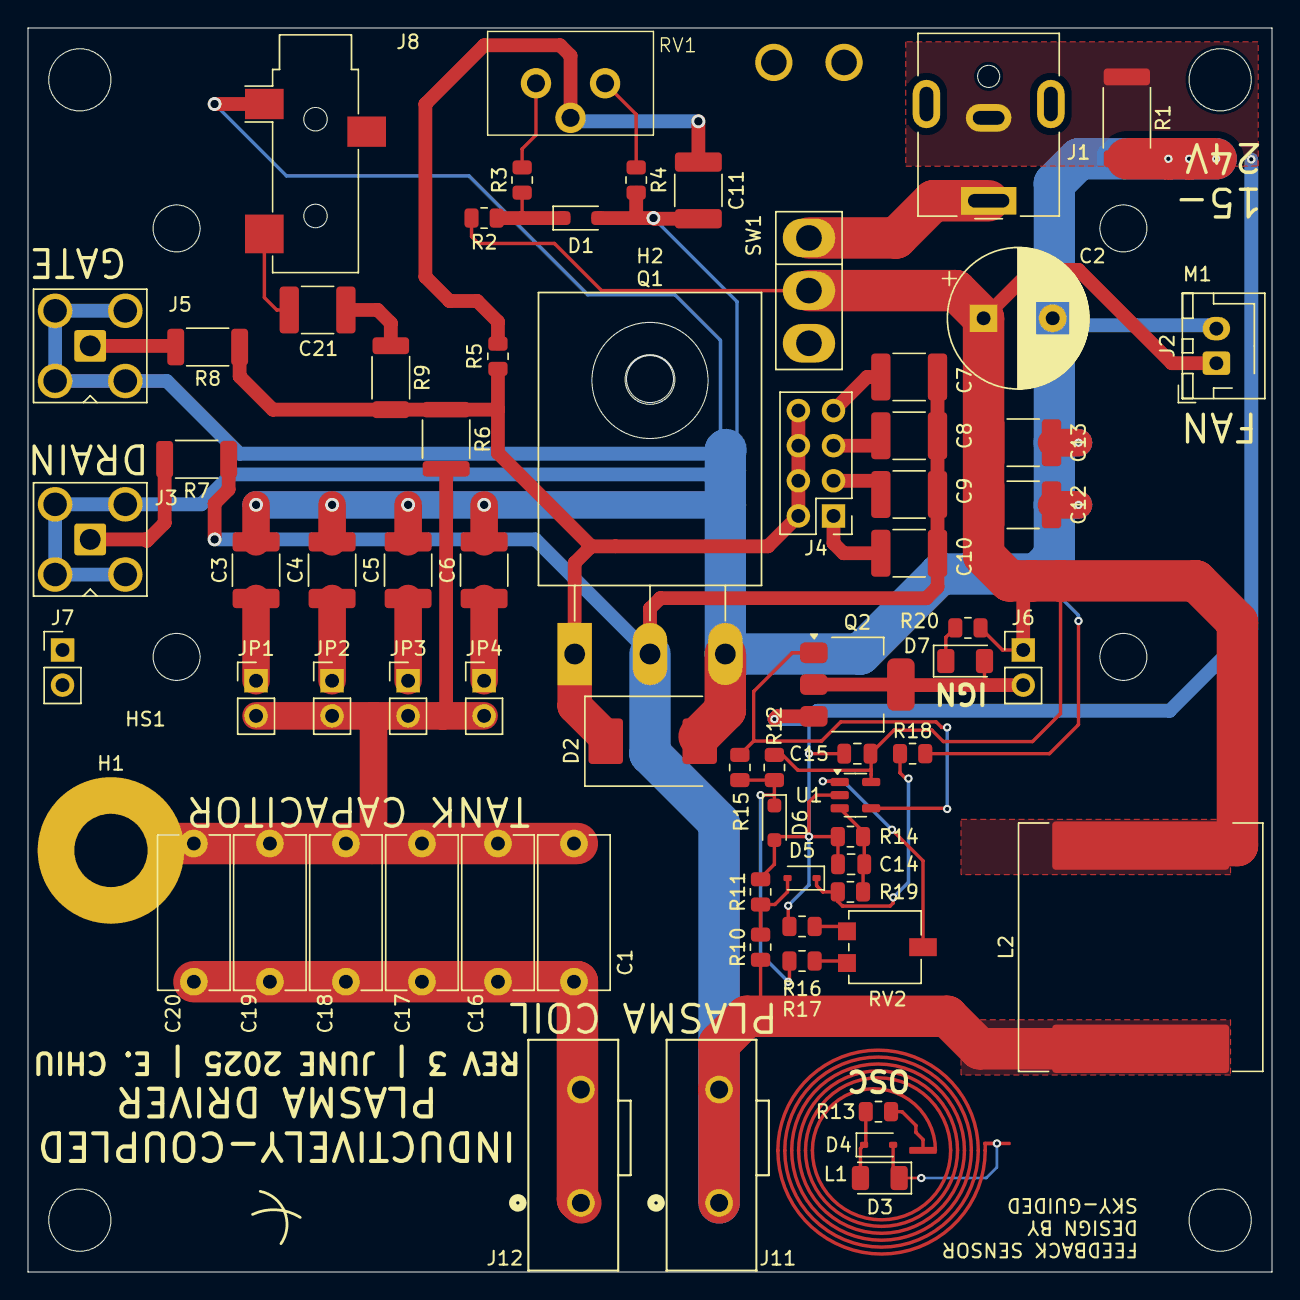
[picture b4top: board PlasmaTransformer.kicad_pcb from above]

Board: 2 copper layers, 90.0 x 90.0 mm, 74 parts (0 on the bottom side), 37 nets.
